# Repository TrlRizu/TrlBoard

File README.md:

<h1 align="center">TRL BOARD</h1>
<h3 align="center">ESP32-S3-WROOM-1 Devboard • IMU + Battery Support</h3>

--- 

## Features
 - ESP-32-S3-WROOM-1
 - ICM-42670-P IMU sensor
 - BQ24072RGT Battery Charger 
 - B2B-XH-A_LF__SN_ Connector
 - TPS63060 Buck Boost Converter
 - CH340C USB-UART bridge
 - USB-C connection
 - 1x20 x2 Connector pins (GPIO/GND/5V/3V3)

---

## PCB Schematic & Layout
#### See full [TrlBoard-schematic](schematic.pdf).

The schematic: 

Front: 

Back: 

---

## Renders

---

## Bill Of Materials

The board is manufactured through JLCPCB's PCBA though not complete as the ESP32-S3-WROOM-1 and header pins are going to be hand-soldered.

> For the breakdown of the board's individual components, check check [Components](TrlBoard-Components.csv).

> For the breakdown of the PCBA components, check [Components](bom-JLCPCB-Assembly-Order.csv).

> For the breakdown of the entire cost check (PCBA + ESP32 + Connector pins + resistor) check [BOM](bom.csv) or look below.

# 🧾 Bill of Materials

| Designator | Footprint                    | Quantity | Qty/board | Value           | Link                                                                                                                                                                                                                                                                                                                                                                                                                                                                                                                                                                                                                                                                                                                                                                                                                         | Cost  | Running Cost |
|-------------|------------------------------|-----------|----------------|-----------------|------------------------------------------------------------------------------------------------------------------------------------------------------------------------------------------------------------------------------------------------------------------------------------------------------------------------------------------------------------------------------------------------------------------------------------------------------------------------------------------------------------------------------------------------------------------------------------------------------------------------------------------------------------------------------------------------------------------------------------------------------------------------------------------------------------------------------|-------|---------------|
| PCBA        |                              | 2         |                |                 | JLCPCB                                                                                                                                                                                                                                                                                                                                                                                                                                                                                                                                                                                                                                                                                                                                                                                                                       | 37.99 | 37.99         |
| U2          | ESP32-S3-WROOM-1             | 2         | 1              | ESP32-S3-WROOM-1 | [AliExpress](https://www.aliexpress.com/item/1005008405001510.html?spm=a2g0o.cart.0.0.186438daN5XPTv&mp=1)                                                                                                                                                                                                                                                                                                                                                                                                                                                                                                                                                                                                                                                                                                                   | 11.58 | 49.57         |
| J2, J4      | PinHeader_1x22_P2.54mm_Vertical | 4         | 2              | Conn_01x12      | [AliExpress](https://www.aliexpress.com/item/4000988113226.html?spm=a2g0o.cart.shoppingCartRecommend.1.186438daYJU8y5&gps-id=shoppingCartRecommend&scm=1007.13440.426876.0&scm_id=1007.13440.426876.0&scm-url=1007.13440.426876.0&pvid=39fa2927-4aee-480c-89c2-457762f75e3d&_t=gps-id:shoppingCartRecommend,scm-url:1007.13440.426876.0,pvid:39fa2927-4aee-480c-89c2-457762f75e3d,tpp_buckets:668%232846%238116%232002&pdp_ext_f=%7B%22order%22%3A%221947%22%2C%22eval%22%3A%221%22%2C%22sceneId%22%3A%223440%22%2C%22fromPage%22%3A%22recommend%22%7D&utparam-url=scene%3AshoppingCartRecommend%7Cquery_from%3A%7Cx_object_id%3A4000988113226%7C_p_origin_prod%3A) | 0.9   | 50.47         |
| R1          | 402                          | 2         | 1              | 680k            | [AliExpress](https://www.aliexpress.com/item/1005006098766125.html?spm=a2g0o.cart.0.0.65dd38dayXF0Oh&mp=1)                                                                                                                                                                                                                                                                                                                                                                                                                                                                                                                                                                                                                                                                                                                    | 0.86  | 51.33         |
| MT1         | ICM-42670-P                  | 2         | 1              | ICM-42670-P     | [AliExpress](https://www.aliexpress.com/item/1005009262807766.html?spm=a2g0o.cart.0.0.65dd38dayXF0Oh&mp=1)                                                                                                                                                                                                                                                                                                                                                                                                                                                                                                                                                                                                                                                                                                                    | 3.38  | 54.71         |
|             |                              |            |                |                 | **AliExpress Tax + Shipping Fee**                                                                                                                                                                                                                                                                                                                                                                                                                                                                                                                                                                                                                                                                                                                                                                                             | 2.4   | 57.11         |
|             |                              |            |                |                 | **Total Cost**                                                                                                                                                                                                                                                                                                                                                                                                                                                                                                                                                                                                                                                                                                                                                                                                                 |       | **57.11**     |

Note: I didn't find any 1x22 pin connectors so why not just purchase 1x30pin and then cut off the excess?

---

## Intended purpose

TRL-Board is a flexible devboard aimed to power personal robotic prototypes, with ideas such as: 
- Quadrupped Bot
- Line-follower 
- Robotic Arm Mirrored control

Ideas to follow!

---

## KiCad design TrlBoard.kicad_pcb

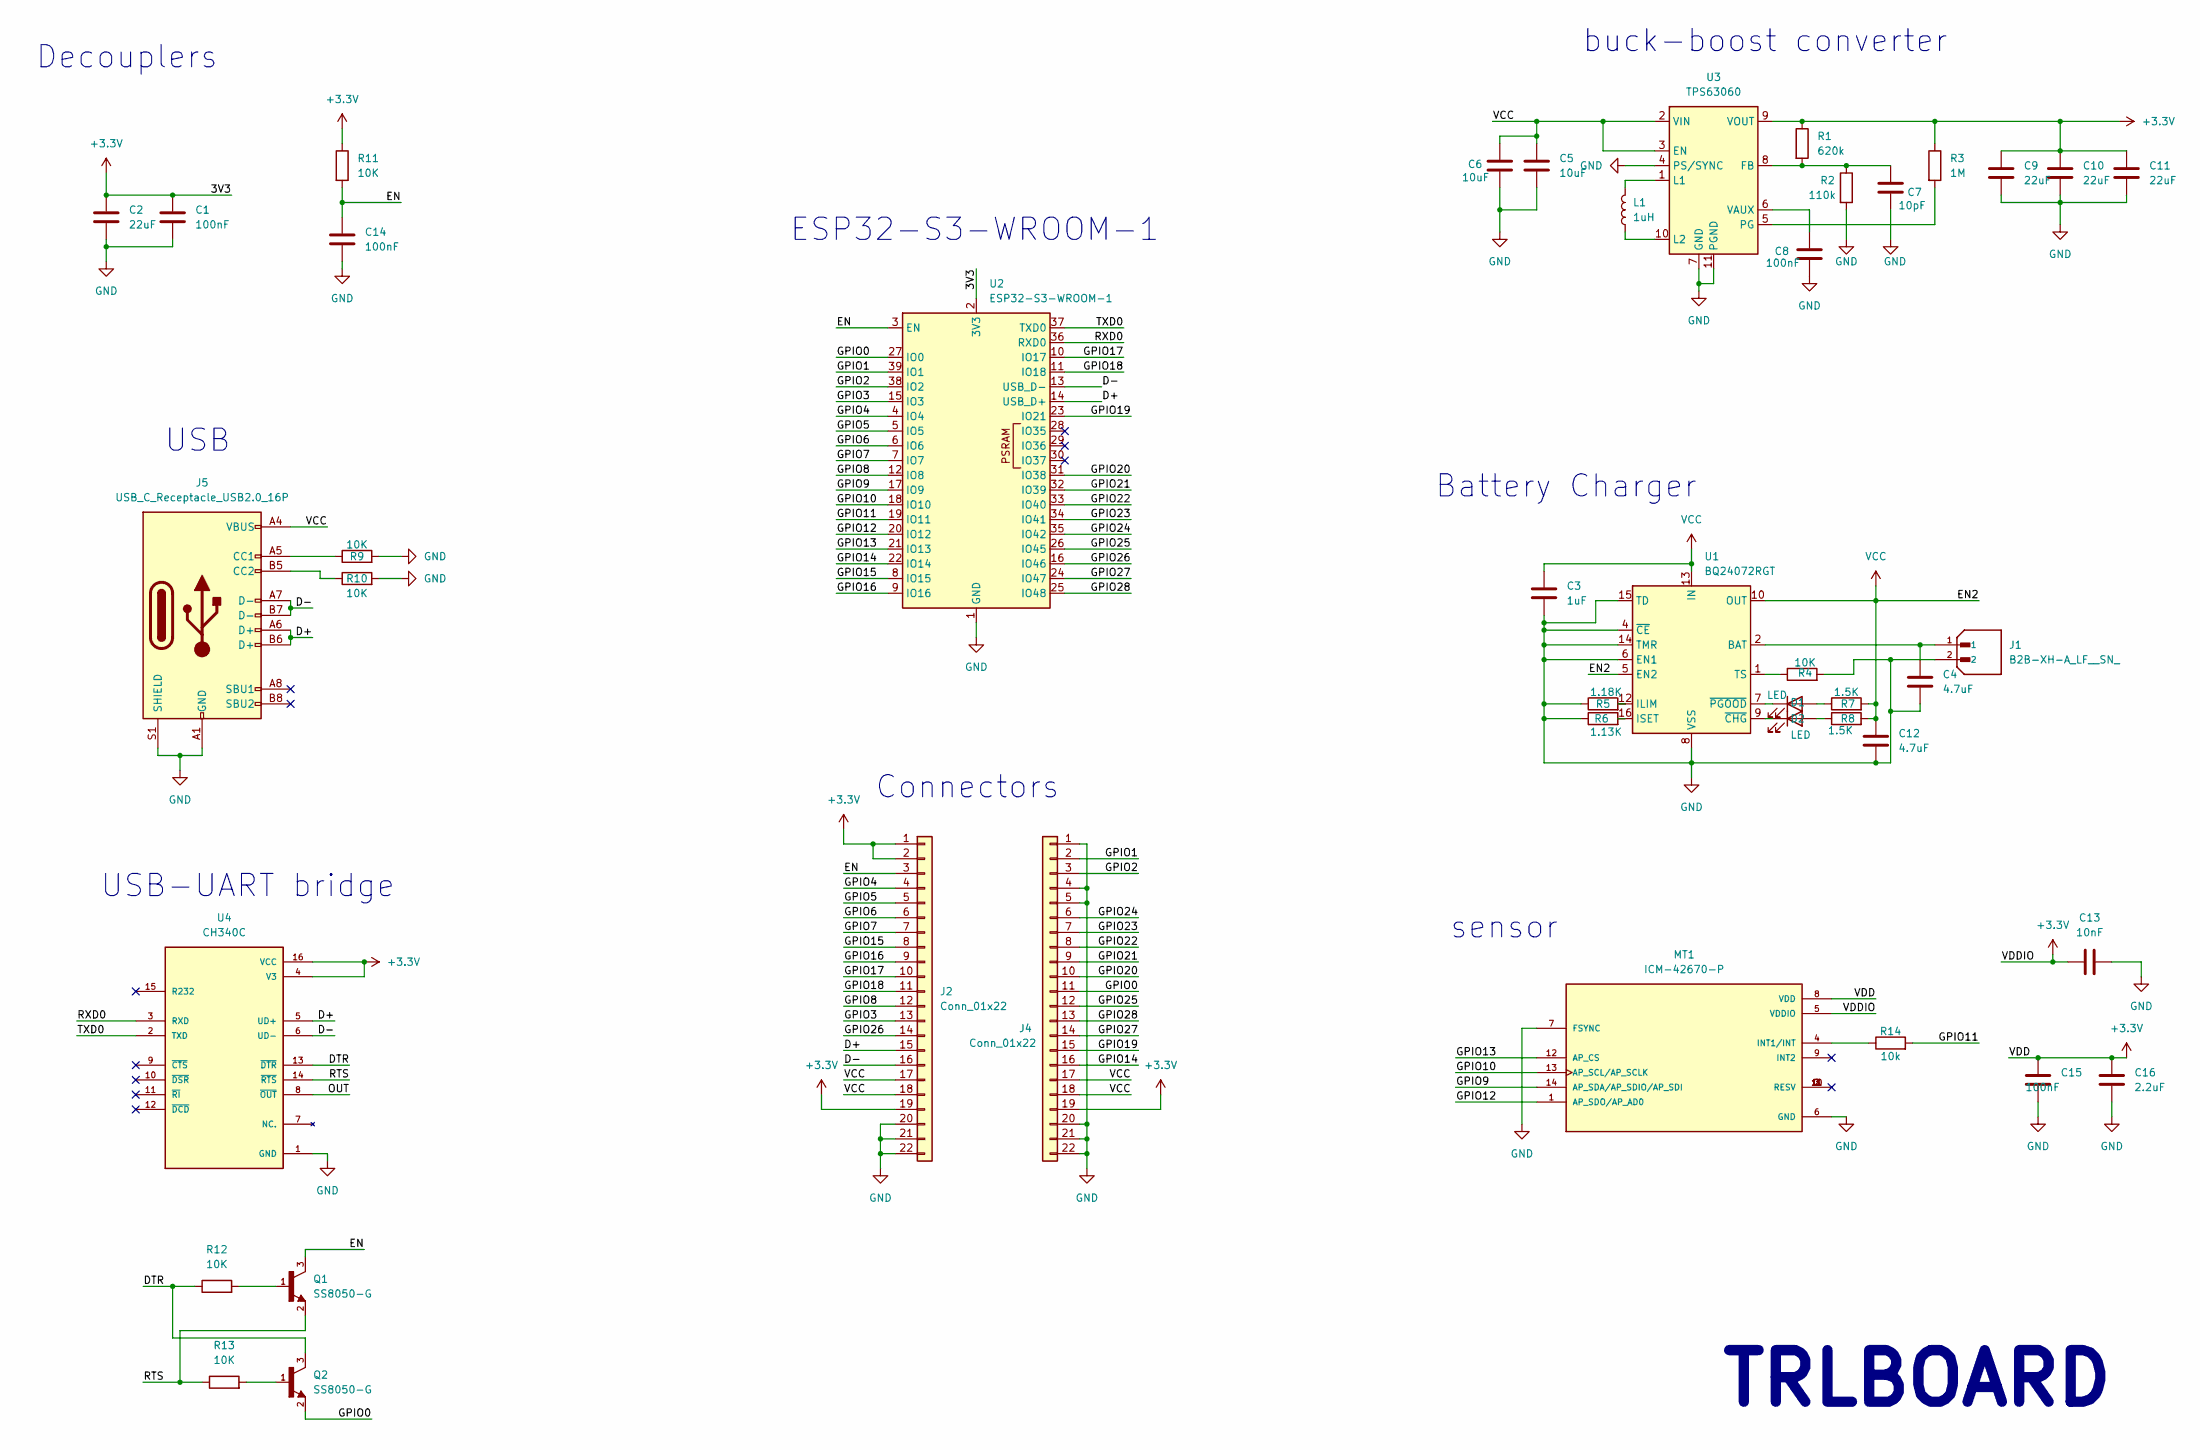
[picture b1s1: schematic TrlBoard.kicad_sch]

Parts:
C1, C8, C14, C15: 100nF; C_0402_1005Metric
C2, C9, C10, C11: 22uF; C_0603_1608Metric
C3: 1uF; C_0402_1005Metric
C4: 4.7uF; C_0402_1005Metric
C5, C6: 10uF; C_0603_1608Metric
C7: 10pF; C_0402_1005Metric
C12: 4.7uF; C_0603_1608Metric
C13: 10nF; C_0402_1005Metric
C16: 2.2uF; C_0402_1005Metric
D1, D2: LED; LED_0402_1005Metric_Pad0.77x0.64mm_HandSolder
J1: B2B-XH-A_LF__SN_; JST_B2B-XH-A_LF__SN_; PARTREV N/A
J2, J4: Conn_01x22; PinHeader_1x22_P2.54mm_Vertical
J5: USB_C_Receptacle_USB2.0_16P; USB_C_Receptacle_HRO_TYPE-C-31-M-12
L1: 1uH; L_0402_1005Metric
MT1: ICM-42670-P; XDCR_ICM-42670-P; PARTREV 1.1
Q1, Q2: SS8050-G; TRANS_SS8050-G; PARTREV A
R1: 620k; R_0402_1005Metric
R2: 110k; R_0402_1005Metric
R3: 1M; R_0603_1608Metric
R4, R9, R10, R11, R12, R13: 10K; R_0402_1005Metric
R5: 1.18K; R_0402_1005Metric
R6: 1.13K; R_0402_1005Metric
R7, R8: 1.5K; R_0402_1005Metric
R14: 10k; R_0402_1005Metric
U1: BQ24072RGT; VQFN-16-1EP_3x3mm_P0.5mm_EP1.6x1.6mm
U2: ESP32-S3-WROOM-1
U3: TPS63060; Texas_S-PWSON-N10_ThermalVias
U4: CH340C; SOIC127P600X180-16N; PARTREV 2G

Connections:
+3.3V: C1.2, C2.1, C9.1, C10.1, C11.1, C13.1, C15.1, C16.1, J2.1, J2.2, J2.19, J4.19, MT1.5 (VDDIO), MT1.8 (VDD), R1.1, R3.1, R11.1, U2.2 (3V3), U3.9 (VOUT), U4.4 (V3), U4.16 (VCC)
/D+: J2.15, J5.A6 (D+), J5.B6 (D+), U2.14 (USB_D+), U4.5 (UD+)
/D-: J2.16, J5.A7 (D-), J5.B7 (D-), U2.13 (USB_D-), U4.6 (UD-)
/DTR: Q2.3, R12.1, U4.13 (~DTR)
/EN: C14.1, J2.3, Q1.3, R11.2, U2.3 (EN)
/GPIO0: J4.11, Q2.2, U2.27 (IO0)
/GPIO1: J4.2, U2.39 (IO1)
/GPIO2: J4.3, U2.38 (IO2)
/GPIO3: J2.13, U2.15 (IO3)
/GPIO4: J2.4, U2.4 (IO4)
/GPIO5: J2.5, U2.5 (IO5)
/GPIO6: J2.6, U2.6 (IO6)
/GPIO7: J2.7, U2.7 (IO7)
/GPIO8: J2.12, U2.12 (IO8)
/GPIO9: MT1.14 (AP_SDA/AP_SDIO/AP_SDI), U2.17 (IO9)
/GPIO10: MT1.13 (AP_SCL/AP_SCLK), U2.18 (IO10)
/GPIO11: R14.2, U2.19 (IO11)
/GPIO12: MT1.1 (AP_SDO/AP_AD0), U2.20 (IO12)
/GPIO13: MT1.12 (AP_CS), U2.21 (IO13)
/GPIO14: J4.16, U2.22 (IO14)
/GPIO15: J2.8, U2.8 (IO15)
/GPIO16: J2.9, U2.9 (IO16)
/GPIO17: J2.10, U2.10 (IO17)
/GPIO18: J2.11, U2.11 (IO18)
/GPIO19: J4.15, U2.23 (IO21)
/GPIO20: J4.10, U2.31 (IO38)
/GPIO21: J4.9, U2.32 (IO39)
/GPIO22: J4.8, U2.33 (IO40)
/GPIO23: J4.7, U2.34 (IO41)
/GPIO24: J4.6, U2.35 (IO42)
/GPIO25: J4.12, U2.26 (IO45)
/GPIO26: J2.14, U2.16 (IO46)
/GPIO27: J4.14, U2.24 (IO47)
/GPIO28: J4.13, U2.25 (IO48)
/OUT: U4.8 (~OUT)
/RTS: Q1.2, R13.1, U4.14 (~RTS)
/RXD0: U2.36 (RXD0), U4.3 (RXD)
/TXD0: U2.37 (TXD0), U4.2 (TXD)
GND: C1.1, C2.2, C3.2, C4.2, C5.2, C6.2, C7.2, C8.2, C9.2, C10.2, C11.2, C12.2, C13.2, C14.2, C15.2, C16.2, J1.2, J2.20, J2.21, J2.22, J4.1, J4.4, J4.5, J4.20, J4.21, J4.22, J5.A1 (GND), J5.A12 (GND), J5.B1 (GND), J5.B12 (GND), J5.S1 (SHIELD), MT1.6 (GND), MT1.7 (FSYNC), R2.2, R4.2, R5.1, R6.1, R9.2, R10.2, U1.4 (~CE), U1.6 (EN1), U1.8 (VSS), U1.14 (TMR), U1.15 (TD), U1.17 (VSS), U2.1 (GND), U2.40 (GND), U2.41 (GND), U3.4 (PS/SYNC), U3.7 (GND), U3.11 (PGND), U4.1 (GND)
unnamed: C4.1, J1.1, U1.2 (BAT), U1.3 (BAT)
unnamed: D1.2 (A), R7.1
unnamed: D1.1 (K), U1.7 (~PGOOD)
unnamed: D2.2 (A), R8.1
unnamed: D2.1 (K), U1.9 (~CHG)
unnamed: J5.A5 (CC1), R9.1
unnamed: J5.B5 (CC2), R10.1
unnamed: MT1.4 (INT1/INT), R14.1
unnamed: Q1.1, R12.2
unnamed: Q2.1, R13.2
unnamed: R5.2, U1.12 (ILIM)
unnamed: R6.2, U1.16 (ISET)
unnamed: R4.1, U1.1 (TS)
unnamed: C7.1, R1.2, R2.1, U3.8 (FB)
unnamed: L1.2, U3.1 (L1)
unnamed: L1.1, U3.10 (L2)
unnamed: R3.2, U3.5 (PG)
unnamed: C8.1, U3.6 (VAUX)
VCC: C3.1, C5.1, C6.1, C12.1, J2.17, J2.18, J4.17, J4.18, J5.A4 (VBUS), J5.A9 (VBUS), J5.B4 (VBUS), J5.B9 (VBUS), R7.2, R8.2, U1.5 (EN2), U1.10 (OUT), U1.11 (OUT), U1.13 (IN), U3.2 (VIN), U3.3 (EN)

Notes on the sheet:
sensor
Decouplers
Battery Charger
ESP32-S3-WROOM-1
USB
USB-UART bridge
TRLBOARD
Connectors
buck-boost converter

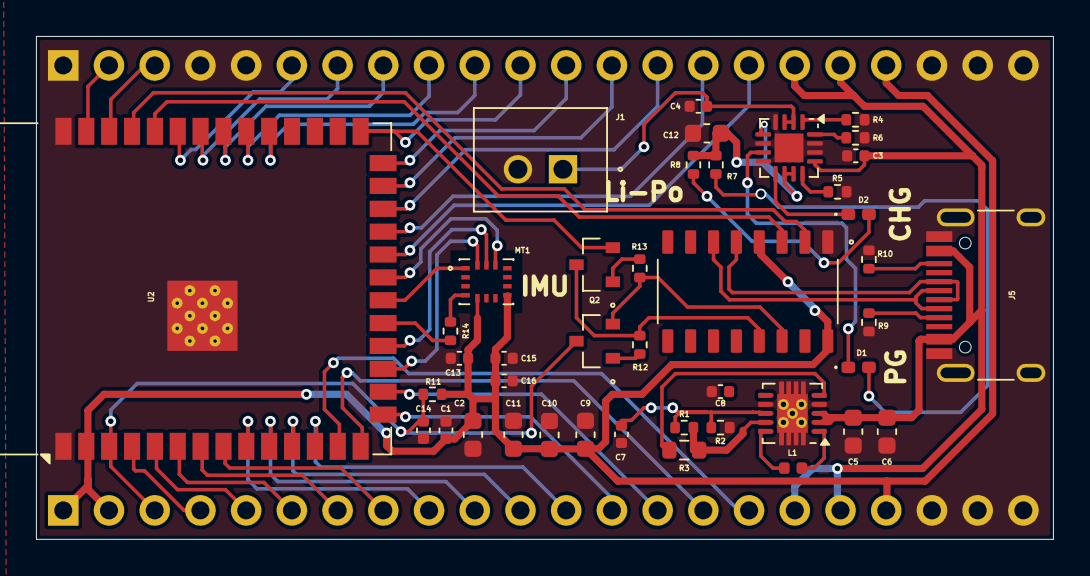
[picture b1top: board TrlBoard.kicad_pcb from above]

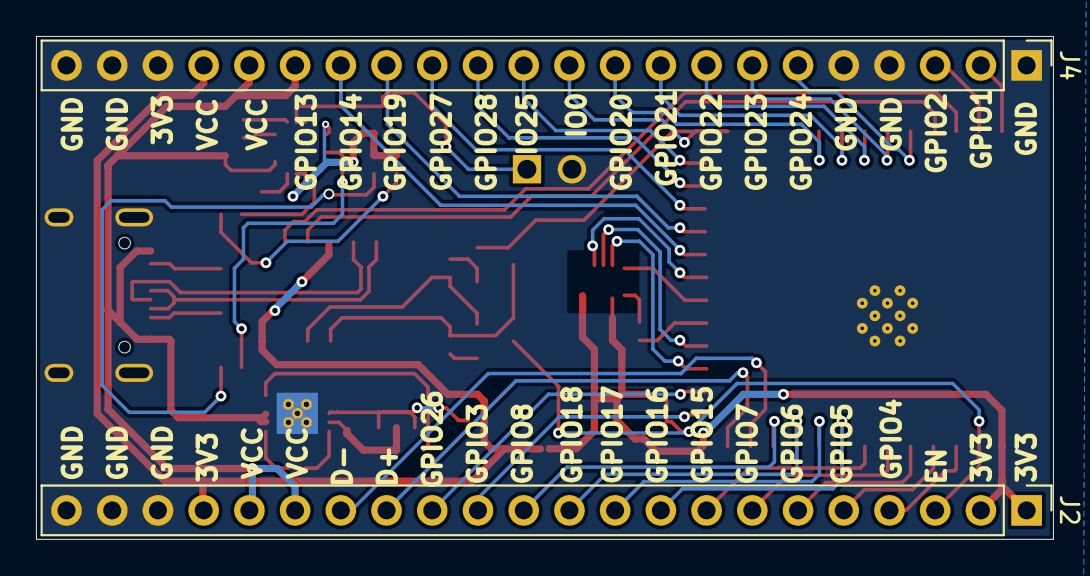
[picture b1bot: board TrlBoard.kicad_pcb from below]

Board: 2 copper layers, 56.5 x 27.9 mm, 44 parts (2 on the bottom side), 57 nets.

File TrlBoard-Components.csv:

Designator,Value,Footprint,LCSC,Quantity,Cost,Running Cost
"C1,C14,C15,C8",100nF,402,C1525,8,0.0096,0.0096
C3,1uF,402,C52923,2,0.0058,0.0154
C4,4.7uF,402,C23733,2,0.0094,0.0248
"C5,C6",10uF,603,C19702,4,0.0224,0.0472
C7,10pF,402,C32949,2,0.0088,0.056
"C10,C11,C2,C9",22uF,603,C59461,8,0.0696,0.1256
C12,4.7uF,603,C19666,2,0.0184,0.144
C13,10nF,402,C15195,2,0.0028,0.1468
C16,2.2uF,402,C12530,2,0.0048,0.1516
"D1,D2",LED,603,C2286,4,0.0224,0.174
J1,B2B-XH-A_LF__SN_,JST_B2B-XH-A_LF__SN_,C158012,3,0.0978,0.2718
J5,USB_C_Receptacle_USB2.0_16P,USB_C_Receptacle_HRO_TYPE-C-31-M-12,C165948,2,0.3388,0.6106
L1,1uH,402,C531288,6,0.3312,0.9418
"Q1,Q2",SS8050-G,TRANS_SS8050-G,C3199946,5,0.3075,1.2493
R1,680k,402,https://www.aliexpress.com/item/1005006098766125.html?spm=a2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,2,0.86,2.1115
R2,120k,603,C25808,2,0.0022,2.1137
R3,1M,603,C22935,2,0.0022,2.1217
R5,1.18K,402,C270651,2,0.008,2.1337
R6,1.13K,402,C67014,2,0.012,2.1361
"R7,R8",1.5K,402,C25867,4,0.0024,2.1445
"R10,R11,R12,R13,R14,R4,R9",10K,402,C25744,14,0.0084,2.1445
"J2, J4",PinHeader_1x22_P2.54mm_Vertical,PinHeader_1x22_P2.54mm_Vertical,https://www.aliexpress.com/item/4000988113226.html?spm=a2g0o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,4,0.9,3.0445
MT1,ICM-42670-P,ICM-42670-P,https://www.aliexpress.com/item/1005009475826927.html?spm=a2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,2,3.38,6.4245
U1,BQ24072RGT,VQFN-16-1EP_3x3mm_P0.5mm_EP1.6x1.6mm,C140288,2,1.878,8.3025
U2,ESP32-S3-WROOM-1,ESP32-S3-WROOM-1,https://www.aliexpress.com/item/1005008405001510.html?spm=a2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,2,11.58,19.8825
U3,TPS63060,Texas_S-PWSON-N10_ThermalVias,C48567,2,1.698,21.5805
U4,CH340C,SOIC127P600X180-16N,C7464026,2,1.167,22.7475

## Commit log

2025-11-07 Initial
2025-11-07 updated bom
2025-11-07 Updated bom + README
2025-11-07 1x30 pin connector
2025-11-07 AliExpress img
2025-11-07 3d model
2025-11-07 Fixed typos
2025-11-10 ICM + Update cost
2025-11-10 Cost update
